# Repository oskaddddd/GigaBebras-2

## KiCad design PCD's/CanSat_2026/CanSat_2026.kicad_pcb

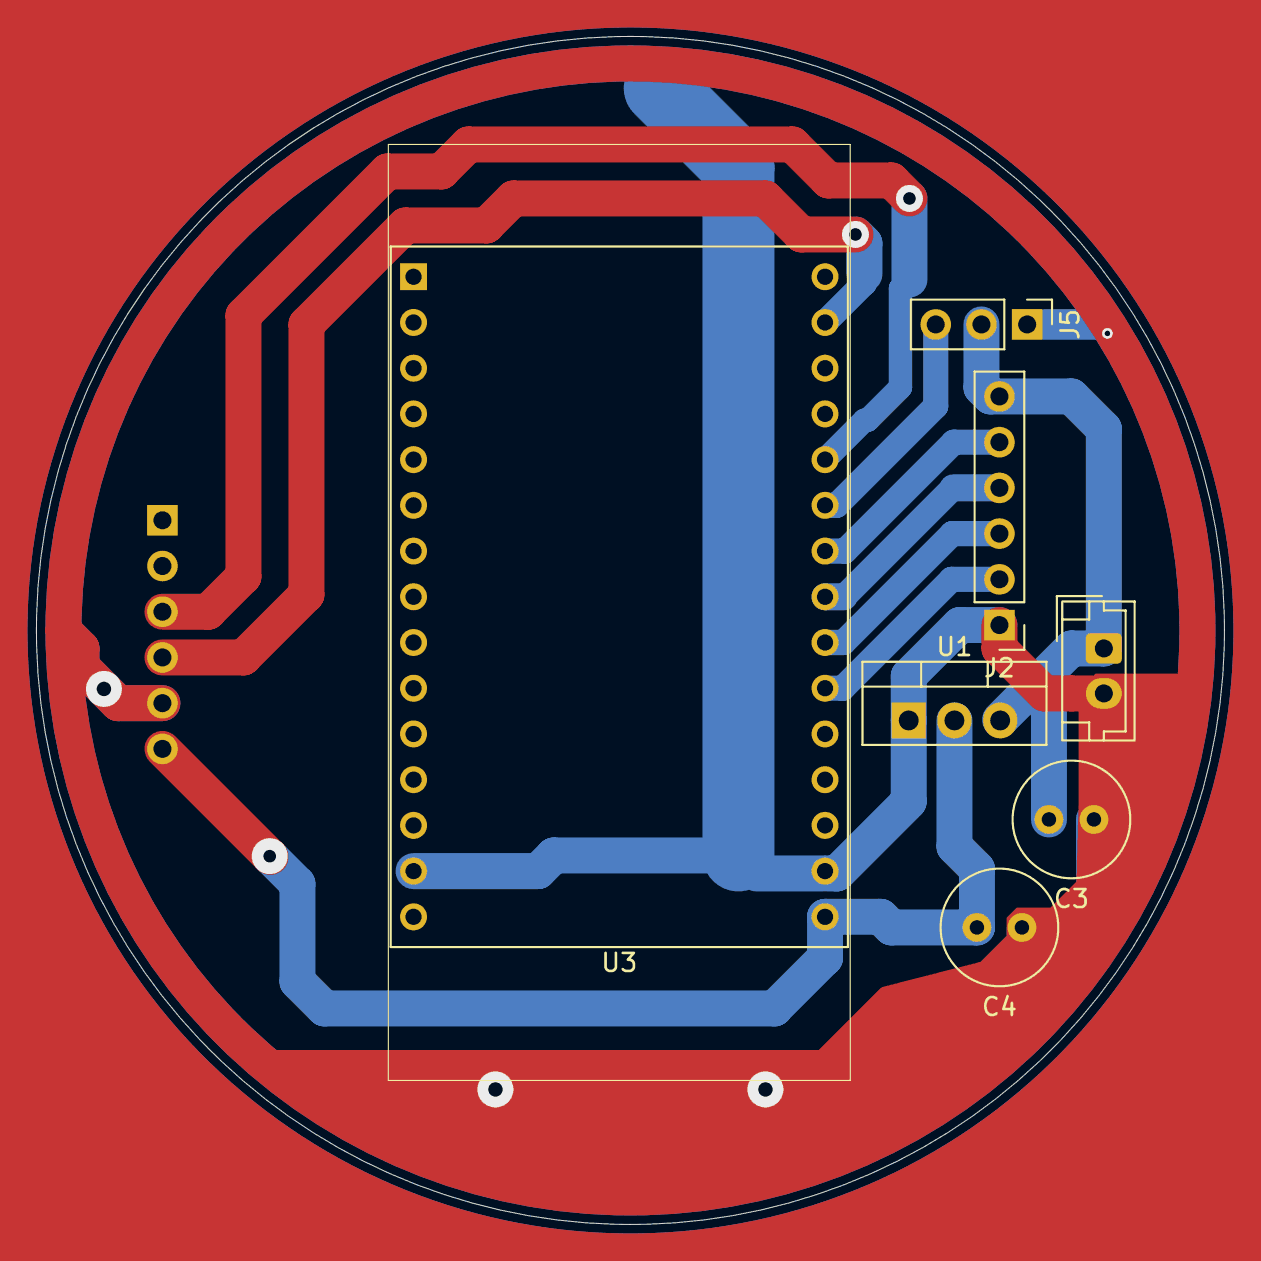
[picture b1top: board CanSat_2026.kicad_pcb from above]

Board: 2 copper layers, 66.0 x 66.0 mm, 8 parts (1 on the bottom side), 9 nets.

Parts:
C3, C4: 10uF_50V; C_Radial_D6.3mm_H11.0mm_P2.50mm
J1: Conn_01x02_Pin; JST_EH_B2B-EH-A_1x02_P2.50mm_Vertical
J2: Conn_01x06; PinHeader_1x06_P2.54mm_Vertical
J3: BMP280; PinHeader_1x06_P2.54mm_Vertical
J5: GPS; PinHeader_1x03_P2.54mm_Vertical
U1: LM1085-3.3; TO-220-3_Vertical
U3: ESP32-WROOM-32D; ESP32-C3-DevKitM-1

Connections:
+3.3V: C4.2, J3.6, U1.2 (VO), U3.2 (VDD)
+5V: C3.2, J1.1, J2.6, J5.2, U1.3 (VI)
GND: C3.1, C4.1, J1.2, J2.1, J3.5, J5.1, U1.1 (GND), U3.1 (GND)
unnamed: J2.2, U3.27 (IO16)
unnamed: J2.3, U3.28 (IO17)
unnamed: J2.4, U3.29 (IO5)
unnamed: J2.5, U3.30 (IO18)
unnamed: J3.3, U3.33 (IO21)
unnamed: J3.4, U3.36 (IO22)

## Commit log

2026-03-12 Initial commit with many unused files
2026-03-12 Trying to get the radio working
2026-03-18 Radio comms mostly work
2026-03-18 fizing the venv thing
2026-03-18 update radio manager
2026-03-24 imma fn cry
2026-03-30 Progrss on esp32 code and pcb version 1
2026-03-30 update PCB
2026-03-30 update to pcb
2026-04-03 rewrite of the read_packets() function in radio manager
2026-04-03 minor fixes to radio manager
2026-04-08 Progress on radio resend request
2026-04-08 PCB updates
2026-04-08 Fix pcb for merge compatibility
2026-04-15 New PCB, progress on esp32 code
2026-04-15 the ground station radios actrually work??? Runs at ~44kilobits/s
2026-04-16 working on it
2026-04-16 esp code compiles
2026-04-19 esp read_packets() works, small fix to radiomanage's radio setup
2026-04-22 Progress on esp32
2026-04-22 Cleanup
2026-04-24 Started working on GUI
2026-04-25 Implemented frequency separation for radios, the receiver side is acting up
2026-04-26 Basic functionality works
2026-04-26 bug fixes on esp32, still vedry slow
2026-04-26 Updates settings and some esp code
2026-04-26 Tahts it, it works (gui's still fucked))
2026-04-28 Fix gps baund, add start button
2026-04-28 implemented a connection packet to initiate communicartion
2026-05-02 slowed in down 2x, it became 4x faster, GUI progress
2026-05-03 gui progress
2026-05-03 parashute wire length caculator
2026-05-06 GUI mostly works
2026-05-18 some stuff
2026-05-18 Made the serial crossplatform
